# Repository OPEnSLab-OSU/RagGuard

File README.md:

# 🚽 RagGuard | [Wiki](https://github.com/OPEnSLab-OSU/RagGuard/wiki)
Project Lead: **Dylan Heisey**
Project Members: **Aiden Olsen**

Sewer pipes carry waste that contains fats, oils, grease (FOG), and other debris that can cause buildup and complications in the system. The RagGuard project aims to protect sensors in these pipes from FOG and debris buildup that can affect the integrity of readings. Using a motor, the RagGuard periodically shakes itself and the sensor to reduce the amount of debris affecting the sensor's performance.

More information about assembly, testing, and operation can be found at the [wiki](https://github.com/OPEnSLab-OSU/RagGuard/wiki).

# ⚙️ RagGuard Programming Instructions

## 🛠️ Arduino UNO Setup:
#### ↬ The Arduino UNO must be setup as a programmer in order to flash the ATtiny85 microcontroller that the controller board uses. In order to do this, complete the following steps:

1. In the arduino IDE do the following: `File > Examples > ArduinoISP > ArduinoISP`
2. Select the ardunio uno board and port
3. Upload the sketch

## 💾 Install ATtiny85 board core:
#### ↬ The ATtiny85 doesnt have an Arduino core by deafault so you must install it to your Arduino IDE as follows:

1. Go to `Settings`
2. Add the following url to the additional board manager URLs:
   ```
   http://drazzy.com/package_drazzy.com_index.json
   ```
3. In the `Board Manager` search for and install `ATtinyCore`

## 🔥 Burn the bootloader:
#### ↬ In order to have the correct clock speed (which is important for timing) the bootloader must be burned in the following manner:

1. Set the board: `Tools > Board > ATTinyCore > ATtiny25/45/85 (no bootloader)`
2. Set clock to `8MHz`
3. Set programmer as `Arduino as ISP`
4. Click `Tools > Burn Bootloader` to burn the bootloader

## 🚀 Upload the code:
#### ↬ Once the bootloader is burned, we can flash a sketch onto the control board using the Arduino as an In-System-Programmer (ISP).

1. Set the board: `Tools > Board > ATTinyCore > ATtiny25/45/85 (no bootloader)`
2. Set clock to `8MHz`
3. Set programmer as `Arduino as ISP`
4. Upload the `RagGuard.ino` sketch to the board w/ `Sketch > Upload Using Programmer`

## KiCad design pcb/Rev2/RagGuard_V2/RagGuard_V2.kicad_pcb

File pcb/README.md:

# Programmer PCB

# Control PCB

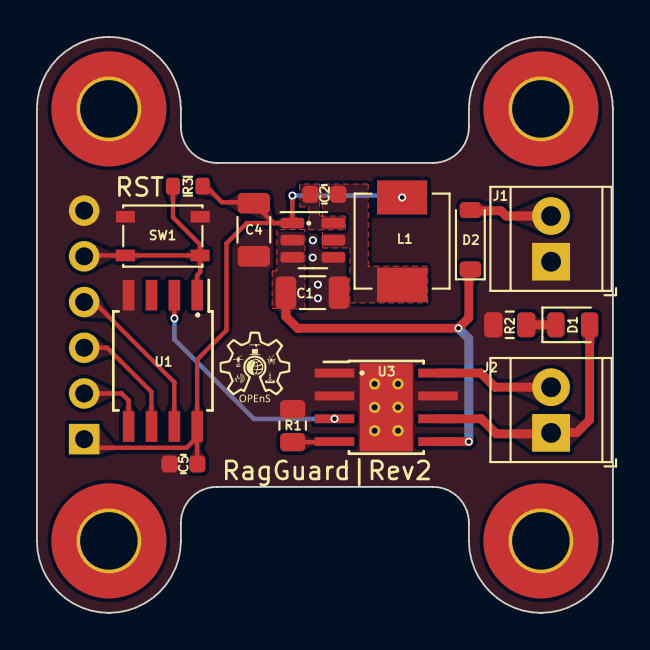
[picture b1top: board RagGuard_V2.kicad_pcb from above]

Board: 2 copper layers, 32.0 x 32.0 mm, 21 parts (1 on the bottom side), 15 nets.

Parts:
C1: 10u; C_1206_3216Metric
C2, C5: 0.1u; C_0603_1608Metric
C4: 22u; C_1206_3216Metric
D1: LED; LED_0805_2012Metric
D2: D; D_SOD-123
H1, H2, H3, H4: MountingHole_Pad; MountingHole_3.2mm_M3_Pad_TopBottom
J1: BATT; TerminalBlock_TE_282834-2_1x02_P2.54mm_Horizontal
J2: MOTOR; TerminalBlock_TE_282834-2_1x02_P2.54mm_Horizontal
J4: PRGM; PinHeader_1x06_P2.54mm_Horizontal
L1: 4.7u; L_Vishay_IHLP-2020
R1: 30k; R_0805_2012Metric
R2: 2k; R_0805_2012Metric
R3: 10k; R_0603_1608Metric
SW1: RST; SW_SPST_PTS810
U1: ATtiny85-20S; SOIC-8W_5.3x5.3mm_P1.27mm
U2: AP63205WU; TSOT-23-6
U3: DRV8871DDA; Texas_HTSOP-8-1EP_3.9x4.9mm_P1.27mm_EP2.95x4.9mm_Mask2.4x3.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

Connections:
+5V: C4.1, C5.1, J4.1, L1.2, R3.1, U1.8 (VCC), U2.1 (FB)
+12V: C1.1, D2.1 (K), U2.2 (EN), U2.3 (IN), U3.5 (VM)
GND: C1.2, C4.2, C5.2, J1.1, J4.6, R1.2, R2.2, SW1.2, U1.4 (GND), U2.4 (GND), U3.1 (GND), U3.2 (IN2), U3.7 (GND), U3.9 (GND)
MOTOR_CTRL: U1.2 (XTAL1/PB3), U3.3 (IN1)
unnamed: D1.2 (A), J2.1, U3.6 (OUT1)
unnamed: D1.1 (K), R2.1
unnamed: D2.2 (A), J1.2
unnamed: J2.2, U3.8 (OUT2)
unnamed: J4.2, U1.5 (AREF/PB0)
unnamed: J4.3, U1.6 (PB1)
unnamed: J4.4, U1.7 (PB2)
unnamed: J4.5, R3.2, SW1.1, U1.1 (~RESET/PB5)
unnamed: C2.2, U2.6 (BST)
unnamed: C2.1, L1.1, U2.5 (SW)
unnamed: R1.1, U3.4 (ILIM)

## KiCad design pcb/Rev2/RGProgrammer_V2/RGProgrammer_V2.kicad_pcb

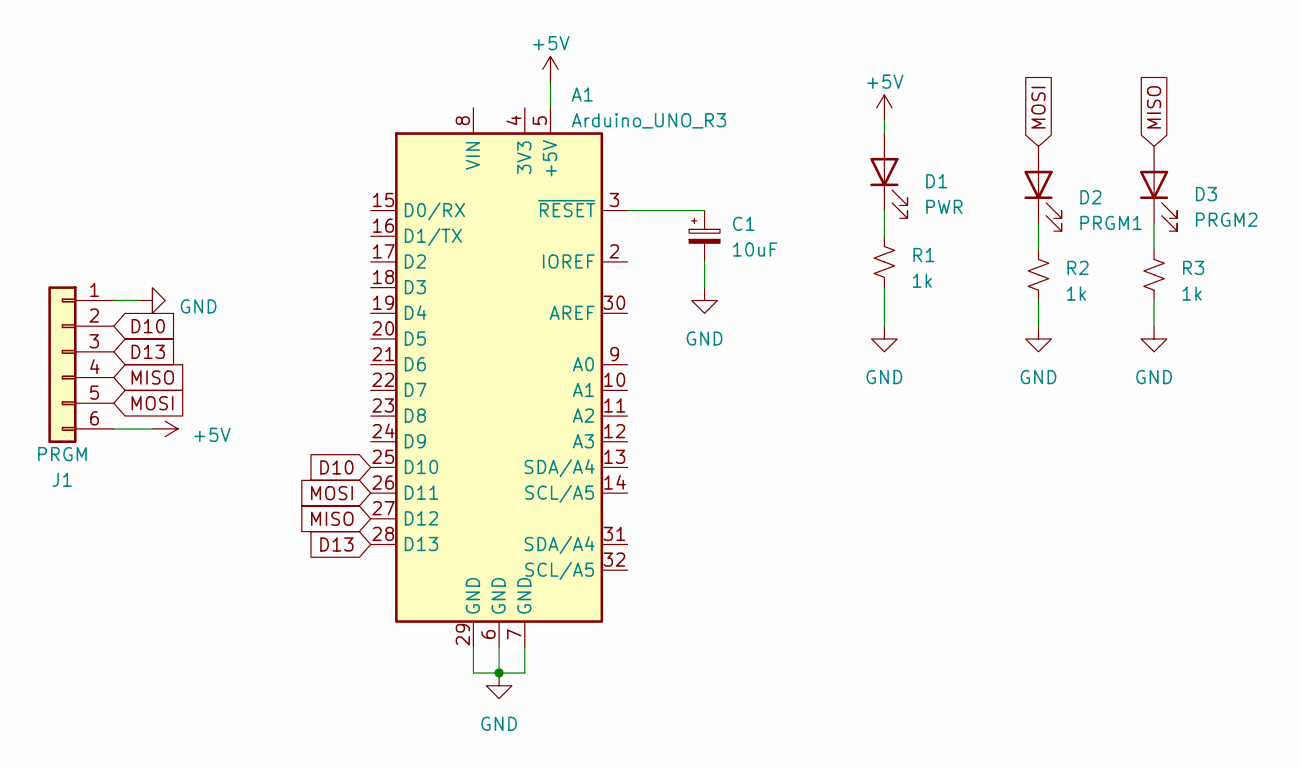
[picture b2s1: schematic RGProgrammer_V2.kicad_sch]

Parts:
A1: Arduino_UNO_R3
C1: 10uF; CP_Elec_4x3
D1: PWR; D_0805_2012Metric
D2: PRGM1; D_0805_2012Metric
D3: PRGM2; D_0805_2012Metric
J1: PRGM; PinSocket_1x06_P2.54mm_Horizontal
R1, R2, R3: 1k; R_0805_2012Metric

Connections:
+5V: A1.5 (+5V), D1.2 (A), J1.6
D10: A1.25 (D10), J1.2
D13: A1.28 (D13), J1.3
GND: A1.6 (GND), A1.7 (GND), A1.29 (GND), C1.2, J1.1, R1.2, R2.2, R3.2
MISO: A1.27 (D12), D3.2 (A), J1.4
MOSI: A1.26 (D11), D2.2 (A), J1.5
unnamed: A1.3 (~RESET), C1.1
unnamed: D1.1 (K), R1.1
unnamed: D2.1 (K), R2.1
unnamed: D3.1 (K), R3.1

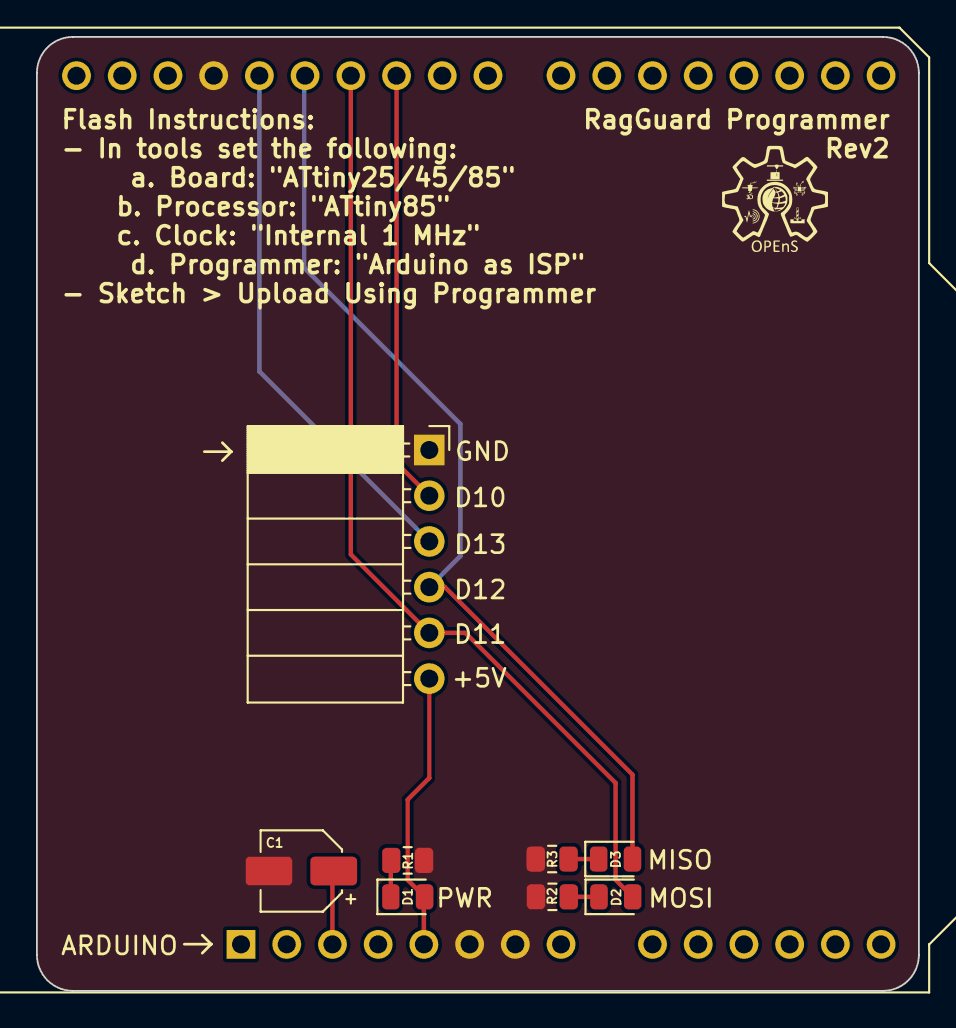
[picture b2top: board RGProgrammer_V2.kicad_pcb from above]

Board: 2 copper layers, 49.0 x 53.0 mm, 9 parts (0 on the bottom side), 10 nets.

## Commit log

2023-04-24 added DS_Store
2023-04-24 Initial Instructions
2023-04-24 init
2023-04-24 Updated readme w/ project description
2023-04-24 added V1 gerber files for both programmer and control board
2023-04-24 Added pcb readme and images
2023-04-24 added kicad files for v1 control board
2023-04-24 fixed gramatical err
2023-05-15 organized Rev1 pcb
2023-05-15 added second revision PCBss
